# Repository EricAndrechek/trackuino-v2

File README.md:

The software and hardware for Trackuino, an open-source APRS tracker based on the Arduino platform. It was designed primarily to track high altitude balloons, so it has other handy features like reading temperature sensors and a buzzer for acoustic location.

Trackuino is intended for use by licensed radio amateurs.

# Features

-   Arduino form factor (support for Arduino Nano, Uno, and Mega)
-   Fully modular, choose the daughterboards you want to use and print/buy them and the motherboard that fits your Arduino
-   Onboard and external LED headers for module status indications
-   Internal/external temperature sensors to read temperature in and outside the payload
-   Active/passive buzzer support to ease acoustic payload location
-   Support for custom additional analog and digital sensors
-   Open source (GPLv2 license), both software and hardware. In other words, do whatever you want with it: modify it, add it to your project, etc. as long as you open-source your modifications as well.

## Modules

Choose whatever modules you want to use and add them onto your motherboard.

### GPS Module

-   Any GPS module that outputs NMEA strings (e.g. SiRF, UBLOX, etc.) is supported
-   GPS used needs 5V, GND, RX, and TX pins

### GSM Cellular Module

-   Allows sending data to a GSM network (e.g. AT&T, T-Mobile, etc.) via web requests or SMS messages
-   Configuration for message format and destination phone number or URL

### Radio Module

-   Radio: Radiometrix's HX1 (300 mW).
-   1200 bauds AFSK using 8-bit PWM
-   Sends out standard APRS position messages (latitude, longitude, altitude, course, speed and time).
-   SMA female plug for radio out

### SD Card Local Storage Module

-   OpenLog SD Card writing for an on-board copy of recorded data
-   Supports CSV format writing of data
-   Raw data dumping option
-   Custom pre-save formatting option (can convert raw analog input to temperature with given formula, etc.)

# Setup

Use the `Download ZIP` button or [click here](https://github.com/EricAndrechek/trackuino-v2/archive/refs/heads/main.zip) to get the source code and board schematics.

## Choosing Boards

Choose the motherboard you want to use based on what Arduino/MCU form factor you plan to use. The larger the Arduino/MCU and therefore motherboard, the more modules you will be able to add.

After selecting your motherboard, you can choose the modules you want to use. You can add as many modules as you want so long as they all fit on the motherboard. One of these modules needs to be the power daughterboard.

**Important**: Pay attention to the voltage your Arduino is using. If you are unsure, check [this page](https://learn.sparkfun.com/tutorials/arduino-comparison-guide/totally-tabular) to find out. If your MCU is 3.3V, you will need to print the 3.3V power daughterboard, if it is 5V, you will need to print the 5V power daughterboard.

Select all motherboards and module daughter boards you would like to use, and find somewhere online to get them printed.

## Soldering

Each module has a readme file that contains instructions for soldering. The boards also include labels on each component detailing what to solder where.

Each board's readme also includes a table of needed components to purchase to be used on your board.

## Software

If you are building for the Arduino platform you need the Arduino IDE. Get it from the [Arduino web site](https://arduino.cc/).

Unzip the software in your sketches directory and load it up by double-clicking on trackuino.ino.

The single most important configuration file is `config.h`. The file is self-documented. Here is where you set up your callsign, module settings, and more.

Some modules, like GSM, allow you to make additional configuration changes in their own custom, self-documented files so that you can do things like specify a JSON format for data to be sent through.

## Flashing

**Important**: When flashing the Arduino, remove the it from the motherboard. After flashing the firmware, you can plug it back in. The GPS, OpenLog, and the host computer share the same serial port on the AVR, so they will conflict when used together.

Within the Arduino IDE, be sure to select the correct board type for your Arduino.

While trackduino.ino is opened in the Arduino IDE, select the `Program` tab and click the `Upload` button.

## Debugging

In order to use serial debugging, you need to enable it in the `config.h` file, upload the code to the Arduino again, and then select the `Serial Monitor` tab.

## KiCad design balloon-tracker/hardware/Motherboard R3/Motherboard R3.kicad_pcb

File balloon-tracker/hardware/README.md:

# Hardware

To use the Trackuino-v2 code on your Arduino, you can either order a print of the PCB designed for your board type, and solder the necessary components onto the board, or you can use the schematics below to wire up your Arduino with a breadboard, protoboard, or something of that type.

## Components

<!-- TODO: update with current BOM -->

You will need the following components if you choose to solder it onto the PCB. Check the notes for each component to see if alternatives are recommended for breadboard wiring.

| Label | Qty | Component                            | Price                               | Provider                                                                                                                                                                                                                                                                                                          | Notes                                                                                                                                                                                                                                                                                                                |
| ----- | --- | ------------------------------------ | ----------------------------------- | ----------------------------------------------------------------------------------------------------------------------------------------------------------------------------------------------------------------------------------------------------------------------------------------------------------------- | -------------------------------------------------------------------------------------------------------------------------------------------------------------------------------------------------------------------------------------------------------------------------------------------------------------------- |
| A1    | 1   | Arduino                              | Depends on what Arduino you go with | [Arduino Store](https://store.arduino.cc/)                                                                                                                                                                                                                                                                        |                                                                                                                                                                                                                                                                                                                      |
| U1    | 1   | Radiometrix HX1                      | $50                                 | [Uptronics](https://store.uputronics.com/index.php?route=product/product&product_id=63), [Radiometrix](https://radiometrix.mybigcommerce.com/hx1-vhf-narrow-band-fm-300mw-transmitter-standard-frequencies-144-390-144-800-and-169-4125mhz/)                                                                      |                                                                                                                                                                                                                                                                                                                      |
| J1    | 1   | SMA Female Connector                 | $1.40                               | [Mouser](https://www.mouser.com/ProductDetail/LPRS/SMA-CONNECTOR?qs=j%252B1pi9TdxUYkOiITvzJM8A%3D%3D), [Uptronics](https://store.uputronics.com/index.php?route=product/product&path=63&product_id=79)                                                                                                            |                                                                                                                                                                                                                                                                                                                      |
|       | 1   | SMA Flexible Extender                | $10                                 | [Uptronics](https://store.uputronics.com/index.php?route=product/product&path=63&product_id=58), [Mouser](https://www.mouser.com/ProductDetail/Amphenol-RF/135109-02-06.00?qs=3WadRV20yGyRMmeZhUPdRQ%3D%3D), [B&H](https://www.bhphotovideo.com/c/product/961489-REG/startech_rpsma10mf_10_rp_sma_to_rp_sma.html) | If antenna is attached straight to board, no flexible extender is needed.                                                                                                                                                                                                                                            |
|       | 1   | Antenna                              | $40                                 | [MFJ](https://mfjenterprises.com/products/mfj-1717s)                                                                                                                                                                                                                                                              |                                                                                                                                                                                                                                                                                                                      |
| U2    | 1   | GPS                                  | $12                                 | [Amazon](https://www.amazon.com/Microcontroller-Compatible-Sensitivity-Navigation-Positioning/dp/B07P8YMVNT)                                                                                                                                                                                                      | Any GPS module will work, so long as it is 5V, and outputs NMEA strings. If you are using the PCB design, having one with TX RX GND and VIN all in a row will allow it to be plug-and-play without any wire re-routing. When purchasing a GPS module, please make note of the GPS limitations on speed and altitude. |
| U3    | 1   | Bi-Directional Logic Level Converter | $3.50                               | [SparkFun](https://www.sparkfun.com/products/12009)                                                                                                                                                                                                                                                               | On a breadboard, you could skip this step and instead build voltage dividers for the RX and TX lines to step them down from 5V to 3.3V.                                                                                                                                                                              |
| U4    | 1   | OpenLog                              | $16.95                              | [SparkFun](https://www.sparkfun.com/products/13712)                                                                                                                                                                                                                                                               |                                                                                                                                                                                                                                                                                                                      |
| U5    | 1   | 3.3V LDO                             | $0.67                               | [Mouser](https://www.mouser.com/ProductDetail/STMicroelectronics/LD1117S33TR?qs=edoyzKMbmhntQZx4BFmoqw%3D%3D)                                                                                                                                                                                                     | Any 3.3V through-hole LDO *should* work for a breadboard, just make note of pin orientations. A LD1117V33 with a footprint of SOT223 is what you are looking for. Here is an example on [Mouser](https://www.mouser.com/ProductDetail/STMicroelectronics/LD1117V50?qs=arR7071Fstdq5MS%2FejBvyQ%3D%3D)                |
| U6    | 1   | 5V LDO                               | $0.67                               | [Mouser](https://www.mouser.com/ProductDetail/STMicroelectronics/LD1117S50TR?qs=eQN2Ig5lfEwsh0kTXN%2FkTg%3D%3D)                                                                                                                                                                                                   | Any 5V through-hole LDO *should* work for a breadboard, just make note of pin orientations. A LD1117V50 with a footprint of SOT223 is what you are looking for.                                                                                                                                                      |
| C1-C3 | 3   | 0.1uF                                | $0.14                               | [Mouser](https://www.mouser.com/ProductDetail/KEMET/C0603C104K3RAC7013?qs=nAEW9fCjKd89XJLxiep6YQ%3D%3D)                                                                                                                                                                                                           | Any 0.1uF Capacitor should work.                                                                                                                                                                                                                                                                                     |
| SW1   | 1   | Push Button                          | $2.50 for 20                        | [Adafruit](https://www.adafruit.com/product/367)                                                                                                                                                                                                                                                                  | You can pretty safely avoid installing this at all and just use the reset button on your Arduino.                                                                                                                                                                                                                    |
| BZ1   | 1   | Buzzer (active or passive)           | $0.30                               | [Active Buzzer - Addicore](https://www.addicore.com/Active-Buzzer-5V-p/ad146.htm), [Passive Busser - Addicore](https://www.addicore.com/Passive-Buzzer-p/ad319.htm)                                                                                                                                               | Active buzzer is more versatile and therefore recommended.                                                                                                                                                                                                                                                           |
| U7    | 2   | TMP36 Temperature Sensor             | $1.60                               | [SparkFun](https://www.sparkfun.com/products/10988)                                                                                                                                                                                                                                                               | One is to be hooked up to terminal blocks to be wired outside of your Trackuino-v2's enclosure, the other is for inside said enclosure.                                                                                                                                                                              |
| P1    | 1   | 2-Wide Terminal Blocks               | $0.65                               | [Mouser](https://www.mouser.com/ProductDetail/CUI-Devices/TB002-500-02BE?qs=vLWxofP3U2x9716kcgva%2Fw%3D%3D)                                                                                                                                                                                                       | Any terminal blocks will work, screwed or not, as long as they fit the same pin dimensions. Alternatively you can skip terminal blocks entirely and solder to the holes they leave on the board. Terminal blocks shouldn't be purchased for a breadboard.                                                            |
| U8    | 1   | 3-Wide Terminal Blocks               | $0.66                               | [Mouser](https://www.mouser.com/ProductDetail/CUI-Devices/TBL004V-508-02BE-2GY?qs=UXgszm6BlbFJXFFgC%2FsssQ%3D%3D)                                                                                                                                                                                                 | Same as previous terminal block note.                                                                                                                                                                                                                                                                                |
| D1-D3 | 3   | LEDs                                 | $4                                  | [Amazon](https://www.amazon.com/JABINCO-Circuit-Assorted-Science-Experiment/dp/B0827KYRFH/ref=sr_1_8?crid=QILAHDHBQAH3&keywords=through-hole+leds&qid=1660157838&sprefix=through-ho%2Caps%2C866&sr=8-8)                                                                                                           | Just any 3 LEDs. Different colors for each makes it easier to differentiate which status LED is which.                                                                                                                                                                                                               |
| R1-R3 | 3   | 330 Ohm Resistors                    | $1.05                               | [SparkFun](https://www.sparkfun.com/products/14490)                                                                                                                                                                                                                                                               | Other resistances would work too, 330 is not an exact requirement.                                                                                                                                                                                                                                                   |

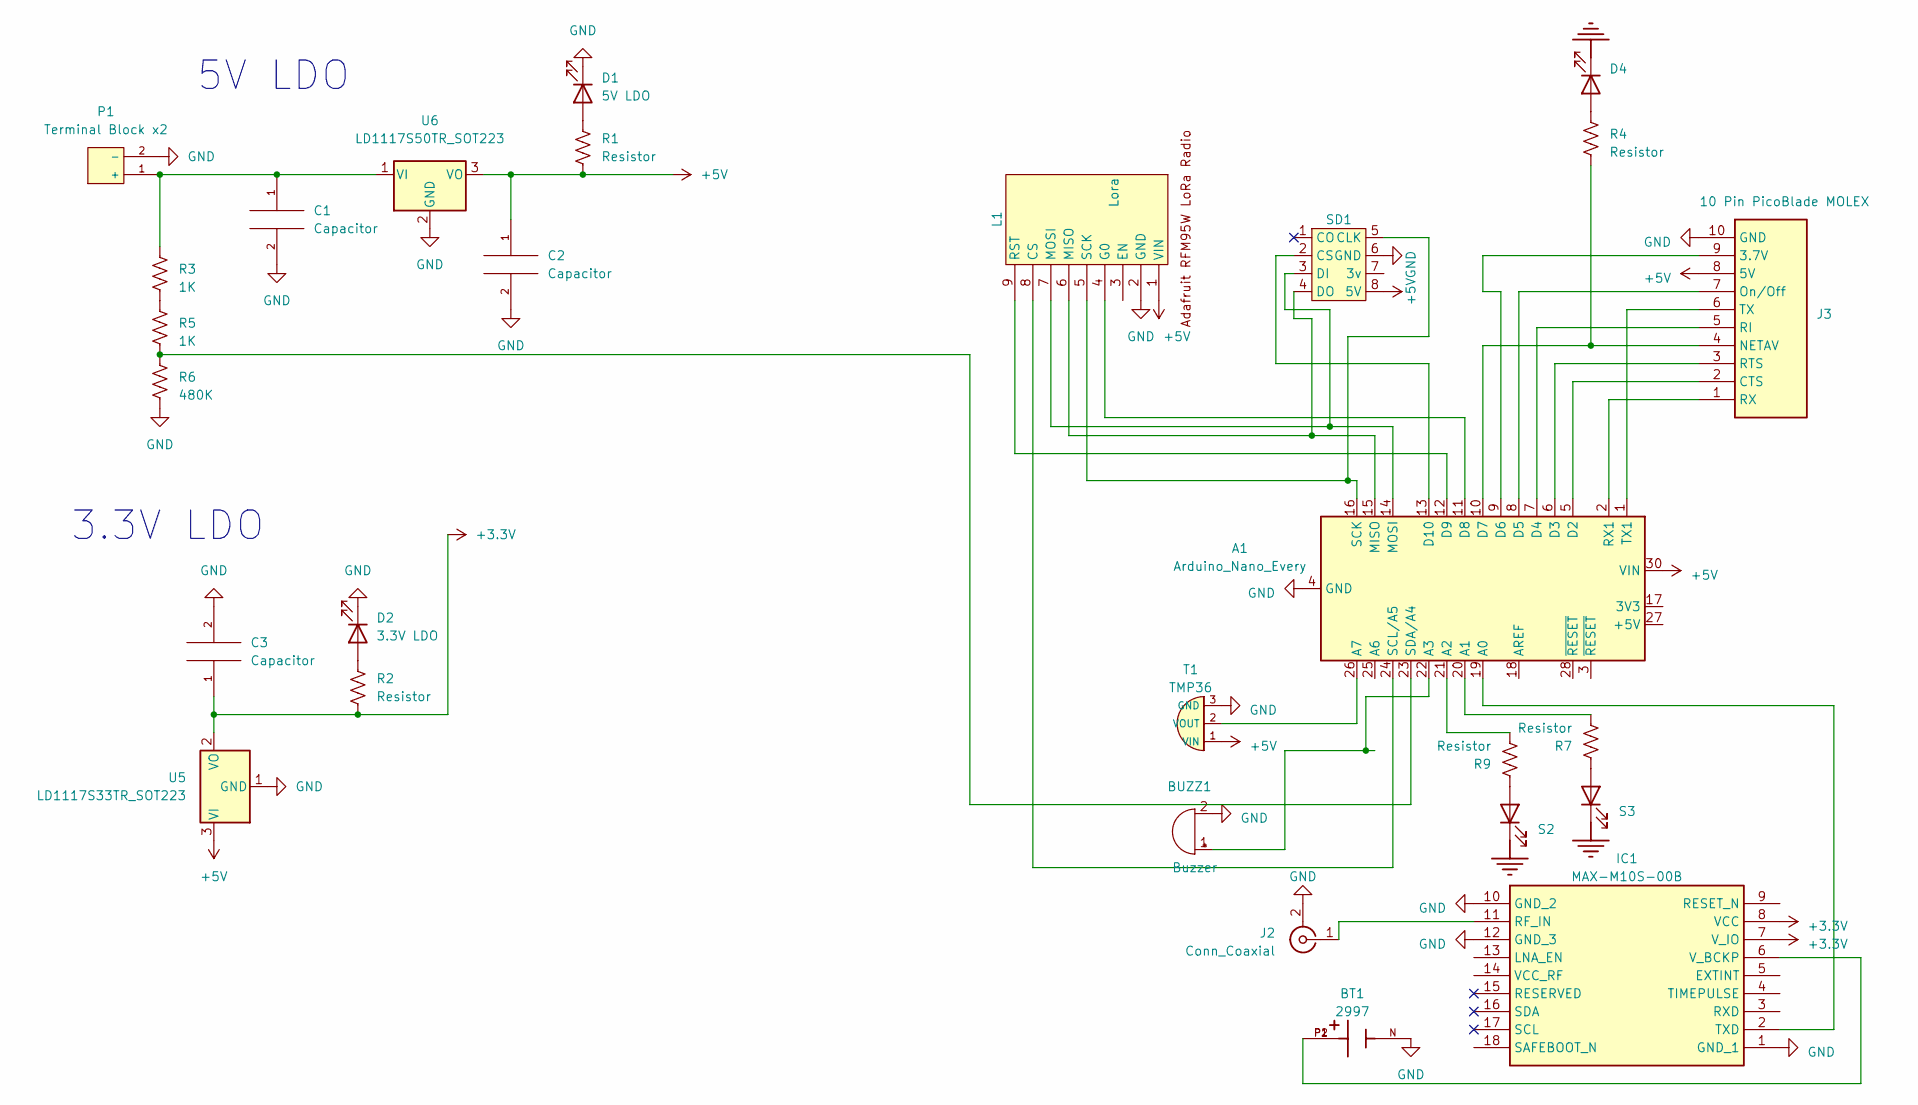
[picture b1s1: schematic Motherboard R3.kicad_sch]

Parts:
A1: Arduino_Nano_Every; Arduino_Nano
BT1: 2997; BAT_2997; PARTREV D
BUZZ1: Buzzer; XDCR_AI-1224-TWT-5V-R
C1, C2, C3: Capacitor; C_1206_3216Metric
D1: 5V LDO; LED_1206_3216Metric
D2: 3.3V LDO; LED_1206_3216Metric
D4: NETAV; LED_1206_3216Metric
IC1: MAX-M10S-00B; MAXM10S00B; Mouser Part Number 377-MAX-M10S-00B
J2: Conn_Coaxial; Molex SMA Edge Mount
J3: 10 Pin PicoBlade MOLEX; Molex_PicoBlade_53048-1010_1x10_P1.25mm_Horizontal; Mouser Part Number 538-53048-1010
L1: Lora; Adafruit LoRa Breakout
P1: Terminal Block x2
R1, R2, R4, R7, R9: Resistor; R_1206_3216Metric
R3, R5: 1K; R_1206_3216Metric
R6: 480K; R_1206_3216Metric
S2, S3: NETAV; LED_1206_3216Metric
SD1: Adafruit 5V SD Breakout Brd+
T1: TMP36
U5: LD1117S33TR_SOT223; SOT-223-3_TabPin2
U6: LD1117S50TR_SOT223; SOT-223-3_TabPin2

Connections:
+3.3V: C3.1, IC1.7 (V_IO), IC1.8 (VCC), R2.2, U5.2 (VO)
+5V: A1.30 (VIN), C2.1, J3.8 (5V), L1.1 (VIN), R1.2, SD1.8 (5V), T1.1 (VIN), U5.3 (VI), U6.3 (VO)
GND: A1.4 (GND), A1.29 (GND), BT1.N, BUZZ1.2 (+), C1.2, C2.2, C3.2, D1.1 (K), D2.1 (K), D4.1 (K), IC1.1 (GND_1), IC1.10 (GND_2), IC1.12 (GND_3), J2.2 (Ext), J3.10 (GND), L1.2 (GND), P1.2 (-), R6.2, S2.1 (K), S3.1 (K), SD1.6 (GND), T1.3 (GND), U5.1 (GND), U6.2 (GND)
unnamed: A1.19 (A0), IC1.2 (TXD)
unnamed: A1.20 (A1), R7.2
unnamed: A1.21 (A2), R9.2
unnamed: A1.22 (A3), BUZZ1.1 (-)
unnamed: A1.26 (A7), T1.2 (VOUT)
unnamed: A1.5 (D2), J3.2 (CTS)
unnamed: A1.6 (D3), J3.3 (RTS)
unnamed: A1.7 (D4), J3.5 (RI)
unnamed: A1.8 (D5), J3.7 (On/Off)
unnamed: A1.9 (D6), J3.9 (3.7V)
unnamed: A1.10 (D7), J3.4 (NETAV), R4.2
unnamed: A1.11 (D8), L1.4 (G0)
unnamed: A1.12 (D9), L1.9 (RST)
unnamed: A1.13 (D10), SD1.2 (CS)
unnamed: A1.15 (MISO), L1.6 (MISO), SD1.4 (DO)
unnamed: A1.14 (MOSI), L1.7 (MOSI), SD1.3 (DI)
unnamed: A1.2 (RX1), J3.1 (RX)
unnamed: A1.16 (SCK), L1.5 (SCK), SD1.5 (CLK)
unnamed: A1.24 (SCL/A5), L1.8 (CS)
unnamed: A1.23 (SDA/A4), R5.2, R6.1
unnamed: A1.1 (TX1), J3.6 (TX)
unnamed: D1.2 (A), R1.1
unnamed: D2.2 (A), R2.1
unnamed: D4.2 (A), R4.1
unnamed: IC1.11 (RF_IN), J2.1 (In)
unnamed: BT1.P1, BT1.P2, IC1.6 (V_BCKP)
unnamed: C1.1, P1.1 (+), R3.1, U6.1 (VI)
unnamed: R3.2, R5.1
unnamed: R9.1, S2.2 (A)
unnamed: R7.1, S3.2 (A)

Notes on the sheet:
3.3V LDO
5V LDO

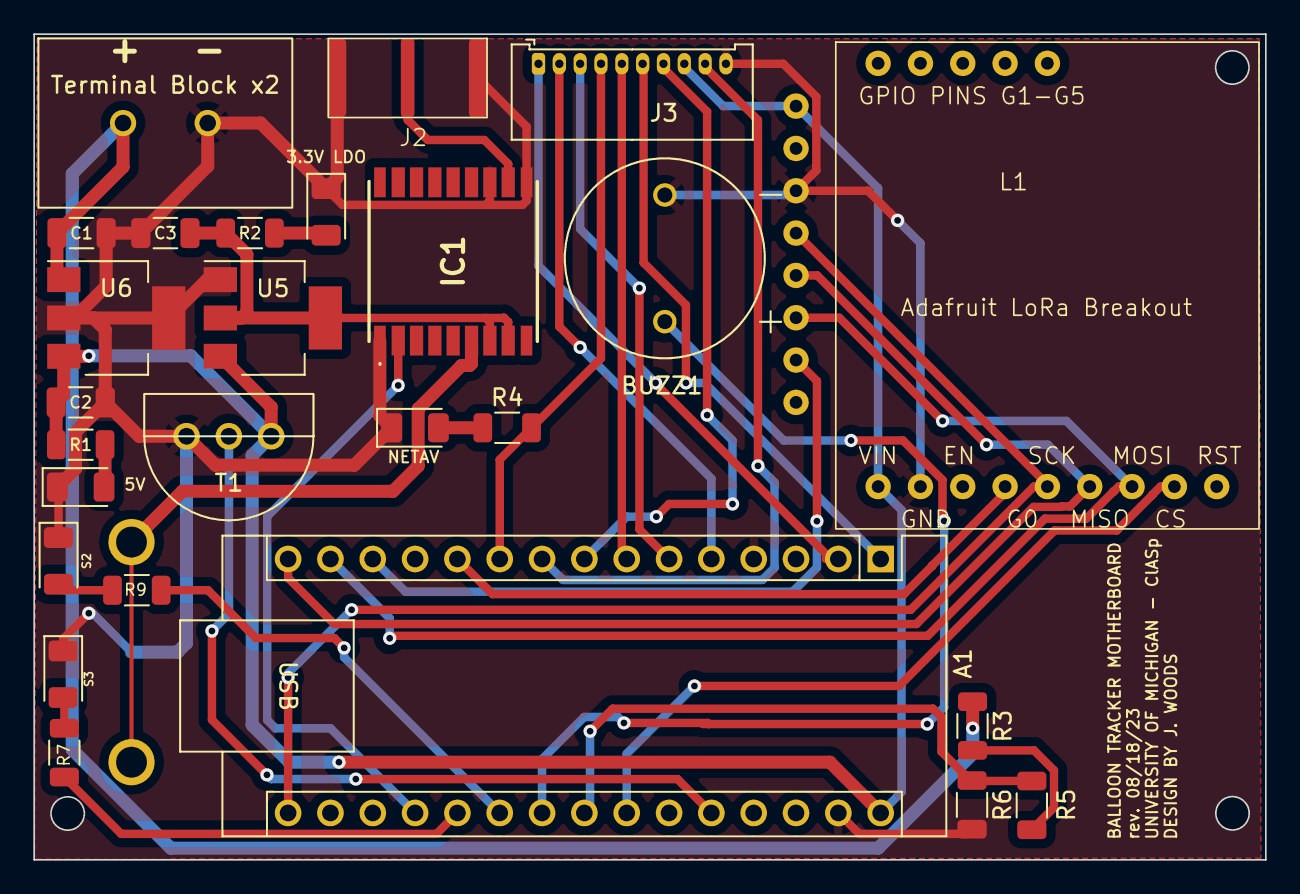
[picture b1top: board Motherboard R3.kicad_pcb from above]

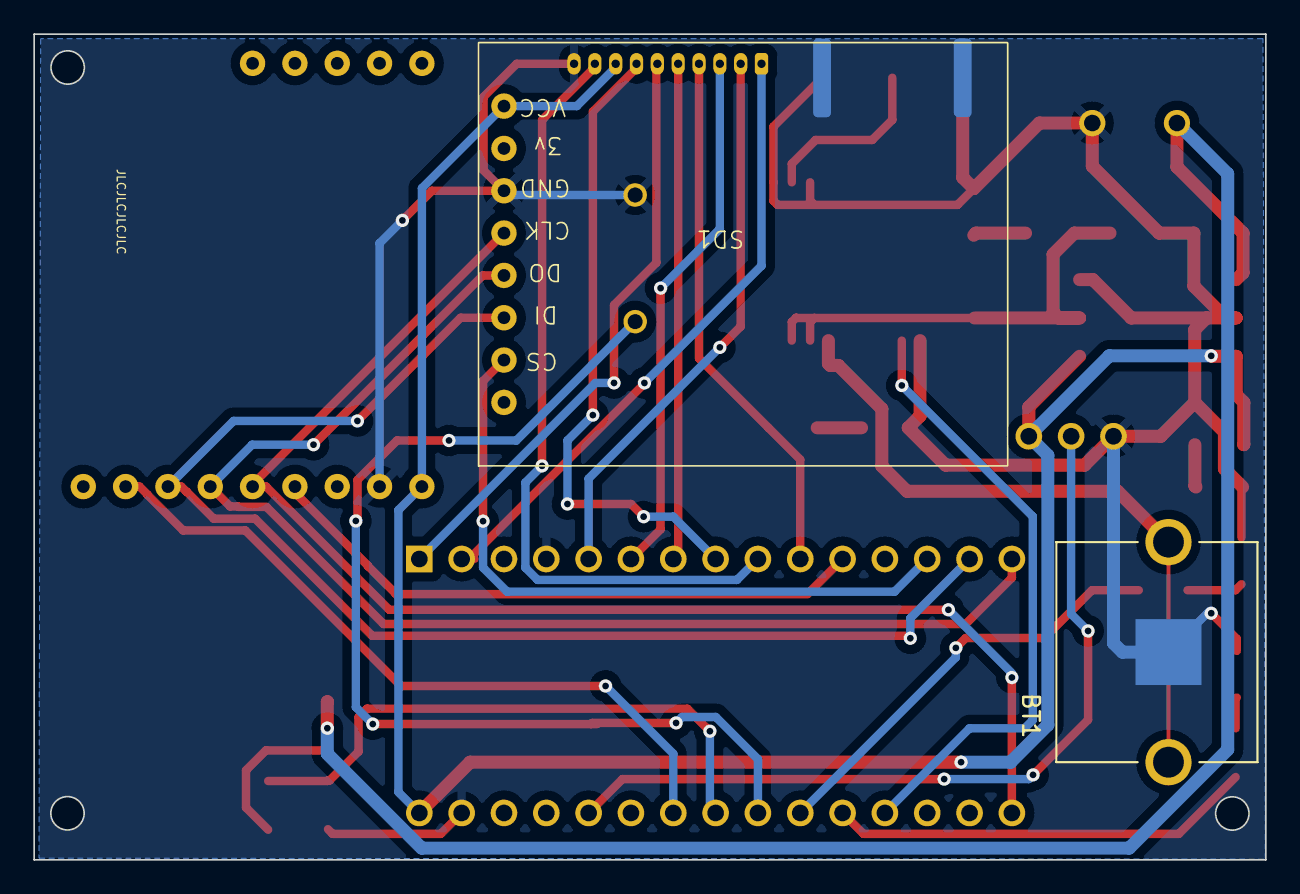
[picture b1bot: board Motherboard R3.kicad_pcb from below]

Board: 2 copper layers, 73.9 x 49.5 mm, 28 parts (2 on the bottom side), 32 nets.

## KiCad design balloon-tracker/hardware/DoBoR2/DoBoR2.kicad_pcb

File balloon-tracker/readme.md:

The software and hardware for Trackuino-v2, an open-source APRS tracker based on the Arduino platform. It was designed primarily to track high altitude balloons, so it has other handy features like reading temperature sensors and a buzzer for acoustic location.

Trackuino is intended for use by licensed radio amateurs.

# Features

- Arduino form factor (support for Arduino Nano, others coming soon:tm:)
- Fully modular, choose the daughterboard you want to use and print/buy them and the motherboard that fits your Arduino
- Onboard and external LED headers for module status indications
- Internal/external temperature sensors to read temperature in and outside the payload
- Active/passive buzzer support to ease acoustic payload location
- Support for custom additional analog and digital sensors
- Open source (GPLv2 license), both software and hardware. In other words, do whatever you want with it: modify it, add it to your project, etc. as long as you open-source your modifications as well.

## Built-In Modules

The following modules are included on the motherboard:

### GPS Module

- UBLOX MAX-M10S GPS chip

### MicroSD Card Local Storage

- MicroSD card writing for an on-board copy of recorded data
- Supports CSV format writing of data
- Raw data dumping option
- Custom pre-save formatting option (can convert raw analog input to temperature with given formula, etc.)

### LoRa Radio Module

- Radio: RFM95W
- 915MHz frequency (tuneable to others for different regions)
- 20dBm output power
- Used to send data in addition to daughterboard modules, allows 2-way communication

### Flight Termination Unit (FTU) Transmitter Module

- Modified [315MHz transmitter](https://www.adafruit.com/product/1095) for sending digital FTU signals

### Buzzer

- Active buzzer for acoustic payload location
- Supports GPS readings for variable buzzing based on altitude or satellite lock

### Temperature Sensors

- Internal and external temperature sensors
- TMP36 analog temperature sensor

### LED Indicators

- Onboard and external LED headers for module status indications
- Customizable LED blinking patterns for different module statuses

## Daughterboard Modules

In addition to the main motherboard, you can attach any one of the following daughterboards to the motherboard via the molex connector for additional functionality.

### GSM Cellular Module

**Note**: Work in progress

- Allows sending data to a GSM network (e.g. AT&T, T-Mobile, etc.) via web requests or SMS messages
- Configuration for message format and destination phone number or URL

### HAM Radio APRS Module

- Radio: DORJI DRA818V
- 1200 baud AFSK using 8-bit PWM
- Sends out standard APRS position messages (latitude, longitude, altitude, course, speed and time), and telemetry data
- SMA plug for radio out

### Iridium Satellite Module

- RockBLOCK 9603 Iridium satellite modem

# Setup

Use the `Download ZIP` button or [click here](https://github.com/EricAndrechek/trackuino-v2/archive/refs/heads/main.zip) to get the source code and board schematics. The hardware is designed in KiCad and the software is written in C++ for the Arduino platform.

Navigate to the `balloon-tracker/hardware` directory to find the KiCad files for the motherboard and daughterboard modules. Navigate to the `balloon-tracker/software` directory to find the Arduino sketch for the firmware.

## Choosing Boards

Choose the motherboard you want to use based on what Arduino/MCU form factor you plan to use.

After selecting your motherboard, you can choose the daughterboard you want to use.

Select all motherboards and daughterboards you would like to use, and find somewhere online to get them printed. You will need to open the KiCad files in KiCad and export the gerber files (and drill files) to send to a PCB printing service.

## Soldering

Each module has a readme file that contains instructions for soldering. The boards also include labels on each component detailing what to solder where.

Each board's readme also includes a table of needed components to purchase to be used on your board.

## Software

If you are building for the Arduino platform you need the Arduino IDE. Get it from the [Arduino web site](https://arduino.cc/).

Unzip the software in your sketches directory and load it up by double-clicking on trackuino.ino.

The single most important configuration file is `config.h`. The file is self-documented. Here is where you set up your callsign, module settings, and more.

Some daughterboards, like GSM, allow you to make additional configuration changes in their own custom, self-documented files so that you can do things like specify a JSON format for data to be sent through.

## Flashing

**Important**: When flashing the Arduino, remove the it from the motherboard. After flashing the firmware, you can plug it back in. The GPS, microSD card module, and the host computer share the same serial port on the AVR, so they will conflict when used together.

Within the Arduino IDE, be sure to select the correct board type for your Arduino.

While `software.ino` is opened in the Arduino IDE, select the `Program` tab and click the `Upload` button.

## Debugging

In order to use serial debugging, you need to enable it in the `config.h` file, upload the code to the Arduino again, and then select the `Serial Monitor` tab.

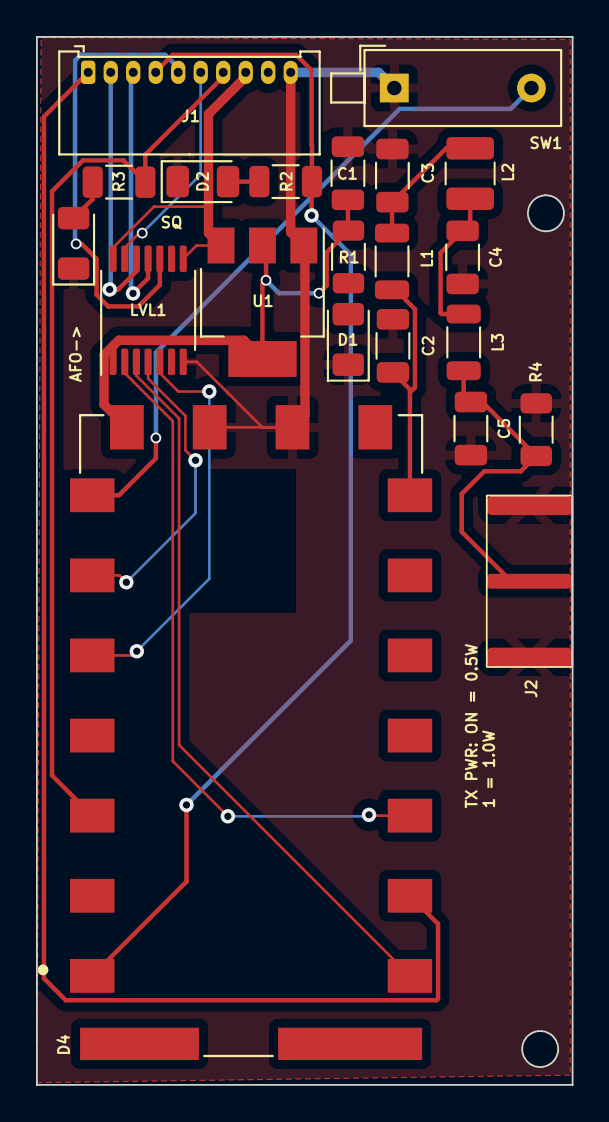
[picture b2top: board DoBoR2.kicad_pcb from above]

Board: 2 copper layers, 29.8 x 58.2 mm, 21 parts (0 on the bottom side), 22 nets.

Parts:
C1: Capacitor; C_1206_3216Metric
C2, C5: 20 pF; C_1206_3216Metric
C3, C4: 36 pF; C_1206_3216Metric
D1: 3.3V LDO; LED_1206_3216Metric
D2: SQUELCH; LED_1206_3216Metric
D3: AF_OUT; LED_1206_3216Metric
D4: DORJI_DRA818V
J1: 10 Pin PicoBlade MOLEX; Molex_PicoBlade_53048-1010_1x10_P1.25mm_Horizontal
J2: Conn_Coaxial; Molex SMA Edge Mount
L1, L3: 56 nH; L_1206_3216Metric
L2: 68 nH; L_1210_3225Metric
LVL1: TXU0104BQAR; TSSOP-14_4.4x5mm_P0.65mm
R1, R2, R3: Resistor; R_1206_3216Metric
R4: 50 ohm; R_1206_3216Metric
SW1: SW_DIP_x01; SW_DIP_SPSTx01_Piano_10.8x4.1mm_W7.62mm_P2.54mm
U1: LD1117S33TR_SOT223; SOT-223-3_TabPin2

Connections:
+3.3V: C1.1, D4.8 (VIN), LVL1.1 (VCC_A), R1.2, U1.2 (VO)
+5V: J1.8 (5V), LVL1.8 (OE), LVL1.14 (VCC_B), U1.3 (VI)
GND: C1.2, C2.2, C3.2, C4.2, C5.2, D1.1 (K), D2.1 (K), D3.1 (K), D4.9 (GND), D4.10 (GND), J1.10 (GND), J2.2 (Ext), LVL1.7 (GND), R4.2, SW1.1, U1.1 (GND)
unnamed: C3.1, L1.2, L2.1
unnamed: C4.1, L2.2, L3.1
unnamed: D1.2 (A), R1.1
unnamed: D2.2 (A), R2.1
unnamed: D3.2 (A), R3.1
unnamed: D4.3 (AF_OUT), J1.7 (On/Off), R3.2
unnamed: C2.1, D4.12 (ANT), L1.1
unnamed: D4.7 (H/L), SW1.2
unnamed: D4.18 (MIC_IN), LVL1.3 (A2)
unnamed: D4.6 (PD), LVL1.4 (A3)
unnamed: D4.5 (PTT), LVL1.5 (A4)
unnamed: D4.16 (RXD), LVL1.2 (A1)
unnamed: D4.1 (SQ), J1.4 (NETAV), R2.2
unnamed: D4.17 (TXD), J1.1 (RX)
unnamed: J1.2 (CTS), LVL1.12 (B2Y)
unnamed: J1.5 (RI), LVL1.10 (B4Y)
unnamed: J1.3 (RTS), LVL1.11 (B3Y)
unnamed: J1.6 (TX), LVL1.13 (B1Y)
unnamed: C5.1, J2.1 (In), L3.2, R4.1

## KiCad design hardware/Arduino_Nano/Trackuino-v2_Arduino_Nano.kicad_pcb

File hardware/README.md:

# Hardware

To use the Trackuino-v2 code on your Arduino, you can either order a print of the PCB designed for your board type, and solder the necessary components onto the board, or you can use the schematics below to wire up your Arduino with a breadboard, protoboard, or something of that type.

## Components

You will need the following components if you choose to solder it onto the PCB. Check the notes for each component to see if alternatives are recommended for breadboard wiring.

| Label | Qty | Component | Price | Provider | Notes |
|---|---|---|---|---|---|
| A1 | 1 | Arduino | Depends on what Arduino you go with | [Arduino Store](https://store.arduino.cc/) |  |
| U1 | 1 | Radiometrix HX1 | $50 | [Uptronics](https://store.uputronics.com/index.php?route=product/product&product_id=63), [Radiometrix](https://radiometrix.mybigcommerce.com/hx1-vhf-narrow-band-fm-300mw-transmitter-standard-frequencies-144-390-144-800-and-169-4125mhz/) |  |
| J1 | 1 | SMA Female Connector | $1.40 | [Mouser](https://www.mouser.com/ProductDetail/LPRS/SMA-CONNECTOR?qs=j%252B1pi9TdxUYkOiITvzJM8A%3D%3D), [Uptronics](https://store.uputronics.com/index.php?route=product/product&path=63&product_id=79) |  |
|  | 1 | SMA Flexible Extender | $10 | [Uptronics](https://store.uputronics.com/index.php?route=product/product&path=63&product_id=58), [Mouser](https://www.mouser.com/ProductDetail/Amphenol-RF/135109-02-06.00?qs=3WadRV20yGyRMmeZhUPdRQ%3D%3D), [B&H](https://www.bhphotovideo.com/c/product/961489-REG/startech_rpsma10mf_10_rp_sma_to_rp_sma.html) | If antenna is attached straight to board, no flexible extender is needed. |
|  | 1 | Antenna | $40 | [MFJ](https://mfjenterprises.com/products/mfj-1717s) |  |
| U2 | 1 | GPS | $12 | [Amazon](https://www.amazon.com/Microcontroller-Compatible-Sensitivity-Navigation-Positioning/dp/B07P8YMVNT) | Any GPS module will work, so long as it is 5V, and outputs NMEA strings. If you are using the PCB design, having one with TX RX GND and VIN all in a row will allow it to be plug-and-play without any wire re-routing. When purchasing a GPS module, please make note of the GPS limitations on speed and altitude. |
| U3 | 1 | Bi-Directional Logic Level Converter | $3.50 | [SparkFun](https://www.sparkfun.com/products/12009) | On a breadboard, you could skip this step and instead build voltage dividers for the RX and TX lines to step them down from 5V to 3.3V. |
| U4 | 1 | OpenLog | $16.95 | [SparkFun](https://www.sparkfun.com/products/13712) |  |
| U5 | 1 | 3.3V LDO | $0.67 | [Mouser](https://www.mouser.com/ProductDetail/STMicroelectronics/LD1117S33TR?qs=edoyzKMbmhntQZx4BFmoqw%3D%3D) | Any 3.3V through-hole LDO *should* work for a breadboard, just make note of pin orientations. A LD1117V33 with a footprint of SOT223 is what you are looking for. Here is an example on [Mouser](https://www.mouser.com/ProductDetail/STMicroelectronics/LD1117V50?qs=arR7071Fstdq5MS%2FejBvyQ%3D%3D) |
| U6 | 1 | 5V LDO | $0.67 | [Mouser](https://www.mouser.com/ProductDetail/STMicroelectronics/LD1117S50TR?qs=eQN2Ig5lfEwsh0kTXN%2FkTg%3D%3D) | Any 5V through-hole LDO *should* work for a breadboard, just make note of pin orientations. A LD1117V50 with a footprint of SOT223 is what you are looking for. |
| C1-C3 | 3 | 0.1uF | $0.14 | [Mouser](https://www.mouser.com/ProductDetail/KEMET/C0603C104K3RAC7013?qs=nAEW9fCjKd89XJLxiep6YQ%3D%3D) | Any 0.1uF Capacitor should work.  |
| SW1 | 1 | Push Button | $2.50 for 20 | [Adafruit](https://www.adafruit.com/product/367) | You can pretty safely avoid installing this at all and just use the reset button on your Arduino. |
| BZ1 | 1 | Buzzer (active or passive) | $0.30 | [Active Buzzer - Addicore](https://www.addicore.com/Active-Buzzer-5V-p/ad146.htm), [Passive Busser - Addicore](https://www.addicore.com/Passive-Buzzer-p/ad319.htm) | Active buzzer is more versatile and therefore recommended.  |
| U7 | 2 | TMP36 Temperature Sensor | $1.60 | [SparkFun](https://www.sparkfun.com/products/10988) | One is to be hooked up to terminal blocks to be wired outside of your Trackuino-v2's enclosure, the other is for inside said enclosure. |
| P1 | 1 | 2-Wide Terminal Blocks | $0.65 | [Mouser](https://www.mouser.com/ProductDetail/CUI-Devices/TB002-500-02BE?qs=vLWxofP3U2x9716kcgva%2Fw%3D%3D) | Any terminal blocks will work, screwed or not, as long as they fit the same pin dimensions. Alternatively you can skip terminal blocks entirely and solder to the holes they leave on the board. Terminal blocks shouldn't be purchased for a breadboard. |
| U8 | 1 | 3-Wide Terminal Blocks | $0.66 | [Mouser](https://www.mouser.com/ProductDetail/CUI-Devices/TBL004V-508-02BE-2GY?qs=UXgszm6BlbFJXFFgC%2FsssQ%3D%3D) | Same as previous terminal block note. |
| D1-D3 | 3 | LEDs | $4 | [Amazon](https://www.amazon.com/JABINCO-Circuit-Assorted-Science-Experiment/dp/B0827KYRFH/ref=sr_1_8?crid=QILAHDHBQAH3&keywords=through-hole+leds&qid=1660157838&sprefix=through-ho%2Caps%2C866&sr=8-8) | Just any 3 LEDs. Different colors for each makes it easier to differentiate which status LED is which. |
| R1-R3 | 3 | 330 Ohm Resistors | $1.05 | [SparkFun](https://www.sparkfun.com/products/14490) | Other resistances would work too, 330 is not an exact requirement. |

## Wiring

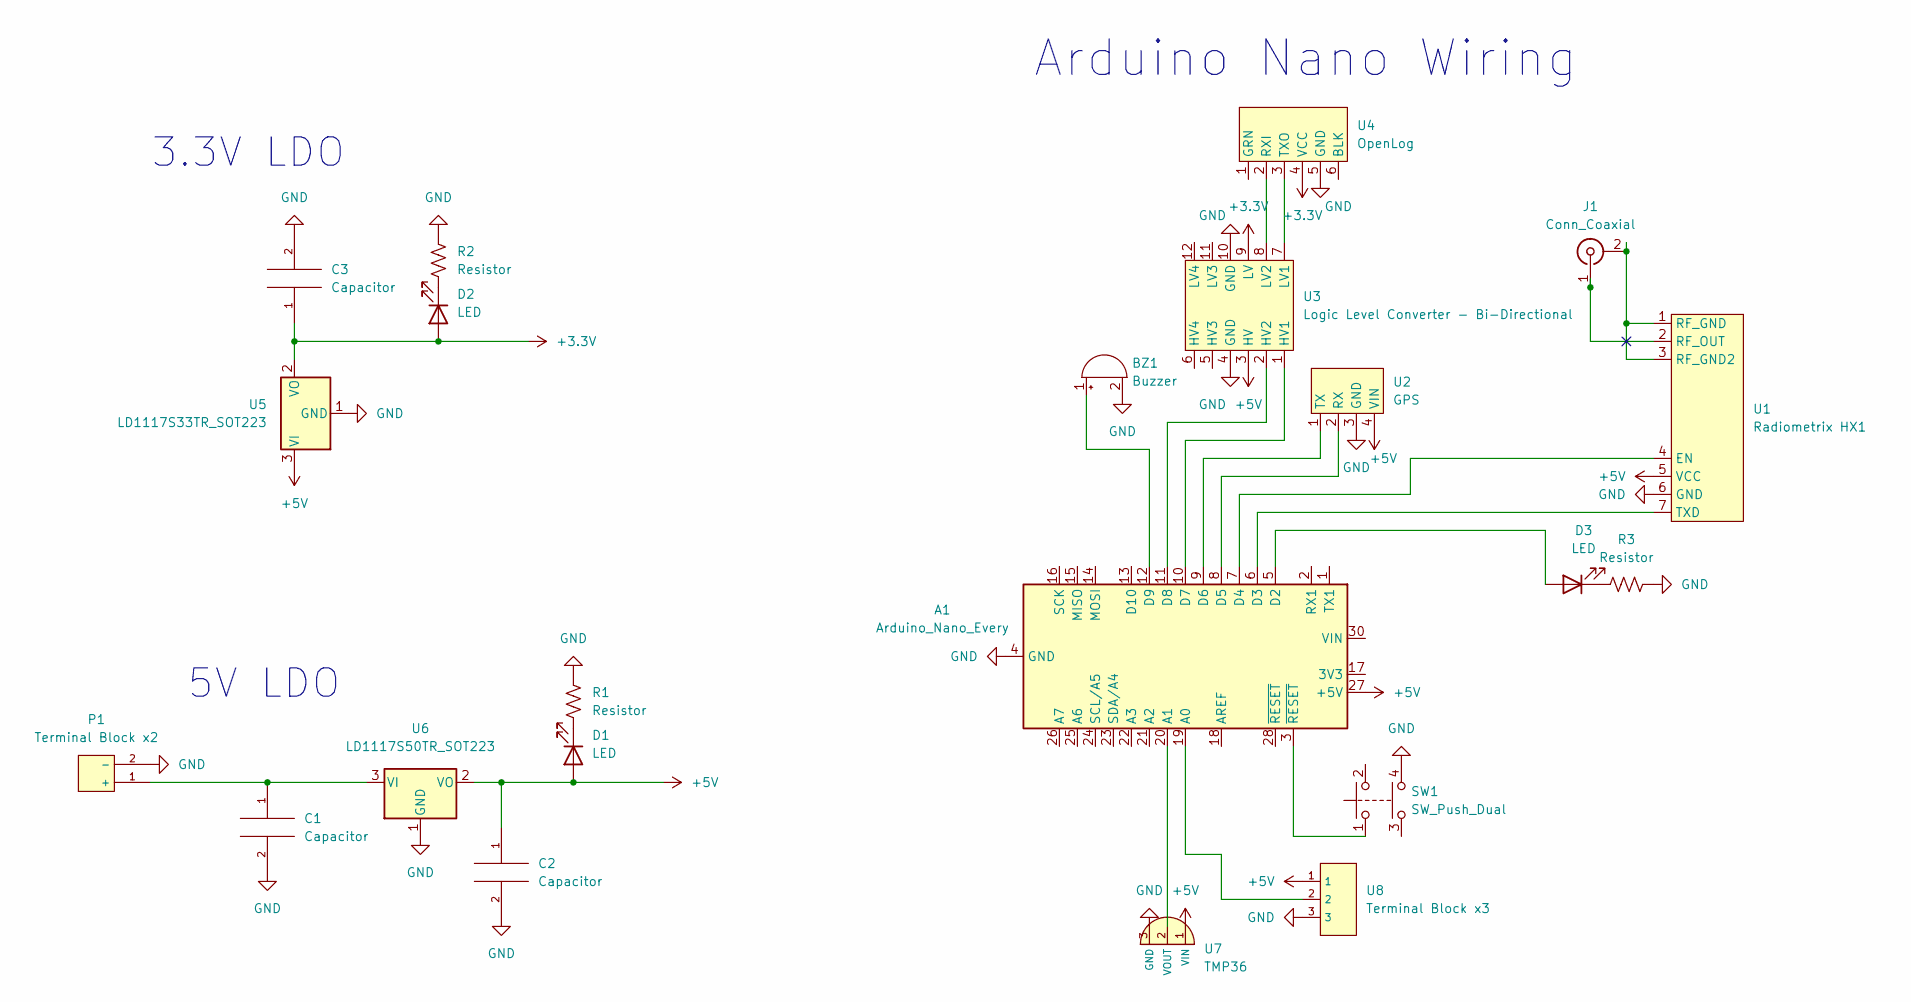
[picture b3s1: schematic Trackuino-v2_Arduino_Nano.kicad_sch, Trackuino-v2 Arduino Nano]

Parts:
A1: Arduino_Nano_Every; Arduino_Nano
BZ1: Buzzer
C1, C2, C3: Capacitor
D1, D2, D3: LED
J1: Conn_Coaxial; SMA Jack
P1: Terminal Block x2
R1, R2, R3: Resistor
SW1: SW_Push_Dual; Button
U1: Radiometrix HX1
U2: GPS
U3: Logic Level Converter - Bi-Directional
U4: OpenLog
U5: LD1117S33TR_SOT223; SOT-223-3_TabPin2
U6: LD1117S50TR_SOT223; SOT-223-3_TabPin2
U7: TMP36
U8: Terminal Block x3

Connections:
+3.3V: C3.1, D2.2 (A), U3.9 (LV), U4.4 (VCC), U5.2 (VO)
+5V: A1.27 (+5V), C2.1, D1.2 (A), U1.5 (VCC), U2.4 (VIN), U3.3 (HV), U5.3 (VI), U6.2 (VO), U7.1 (VIN), U8.1
GND: A1.4 (GND), A1.29 (GND), BZ1.2 (+), C1.2, C2.2, C3.2, P1.2 (-), R1.1, R2.1, R3.1, SW1.4, U1.6 (GND), U2.3 (GND), U3.4 (GND), U3.10 (GND), U4.5 (GND), U5.1 (GND), U6.1 (GND), U7.3 (GND), U8.3
unnamed: A1.3 (~RESET), SW1.1
unnamed: A1.5 (D2), D3.2 (A)
unnamed: A1.6 (D3), U1.7 (TXD)
unnamed: A1.7 (D4), U1.4 (EN)
unnamed: A1.8 (D5), U2.2 (RX)
unnamed: A1.9 (D6), U2.1 (TX)
unnamed: A1.10 (D7), U3.1 (HV1)
unnamed: A1.11 (D8), U3.2 (HV2)
unnamed: A1.12 (D9), BZ1.1 (-)
unnamed: A1.19 (A0), U8.2
unnamed: A1.20 (A1), U7.2 (VOUT)
unnamed: C1.1, P1.1 (+), U6.3 (VI)
unnamed: D1.1 (K), R1.2
unnamed: D2.1 (K), R2.2
unnamed: D3.1 (K), R3.2
unnamed: J1.1 (In), U1.2 (RF_OUT)
unnamed: J1.2 (Ext), U1.1 (RF_GND), U1.3 (RF_GND2)
unnamed: U3.7 (LV1), U4.3 (TXO)
unnamed: U3.8 (LV2), U4.2 (RXI)

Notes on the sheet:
5V LDO
3.3V LDO
Arduino Nano Wiring

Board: 2 copper layers, 22 parts (0 on the bottom side), 22 nets, no tracks yet.

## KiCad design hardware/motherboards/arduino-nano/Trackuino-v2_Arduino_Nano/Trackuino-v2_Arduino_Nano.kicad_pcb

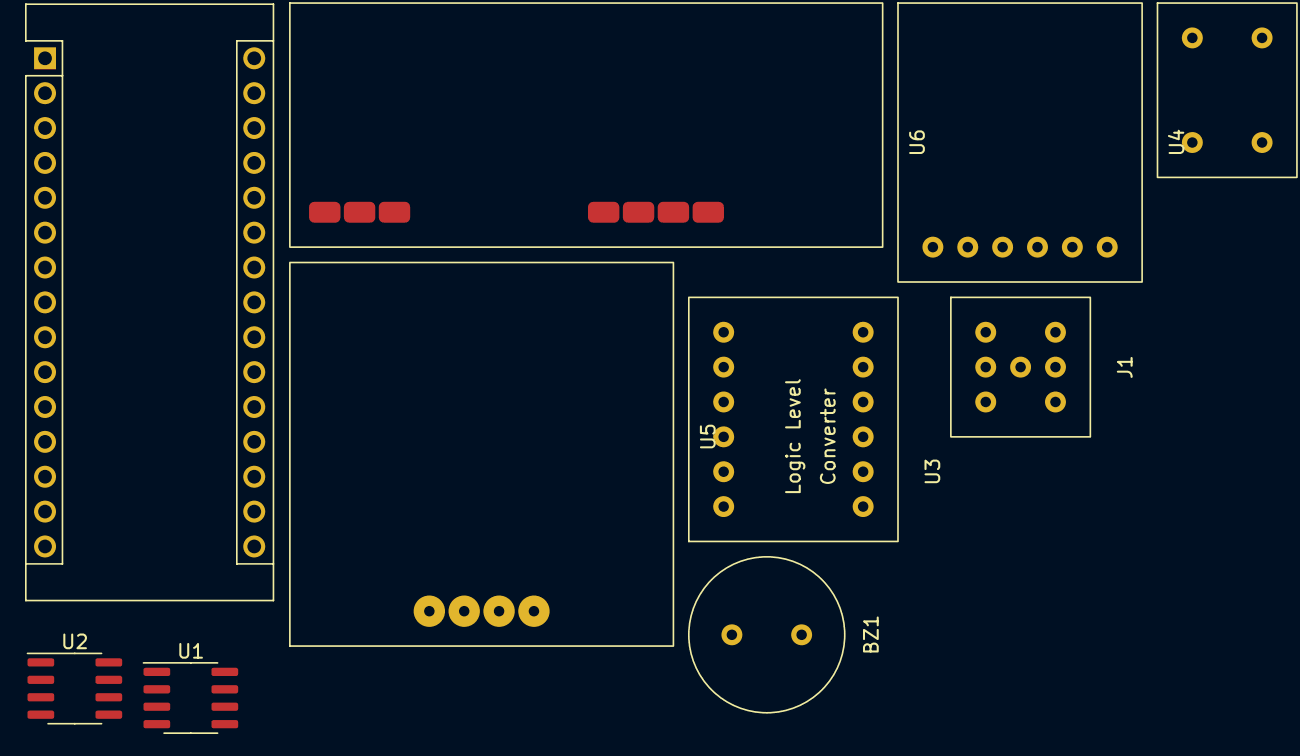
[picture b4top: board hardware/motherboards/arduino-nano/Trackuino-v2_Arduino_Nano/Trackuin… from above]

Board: 2 copper layers, 10 parts (0 on the bottom side), 17 nets, no tracks yet.

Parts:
A1: Arduino_Nano_Every; Arduino_Nano
BZ1: Buzzer
J1: Conn_Coaxial; SMA Jack
SW1: SW_Push_Dual; Button
U1, U2: TMP36xS; SOIC-8_3.9x4.9mm_P1.27mm
U3: Logic Level Converter - Bi-Directional
U4: OpenLog
U5: GPS
U6: Radiometrix HX1

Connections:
+3.3V: U3.9 (LV), U4.4 (VCC)
+5V: A1.27 (+5V), U1.8 (+Vs), U2.8 (+Vs), U3.3 (HV), U5.4 (VIN), U6.5 (VCC)
GND: A1.4 (GND), A1.29 (GND), BZ1.2 (+), SW1.4, U1.4 (GND), U2.4 (GND), U3.4 (GND), U3.10 (GND), U4.5 (GND), U5.3 (GND), U6.6 (GND)
unnamed: A1.3 (~RESET), SW1.1
unnamed: A1.6 (D3), U6.7 (TXD)
unnamed: A1.7 (D4), U6.4 (EN)
unnamed: A1.8 (D5), U5.2 (RX)
unnamed: A1.9 (D6), U5.1 (TX)
unnamed: A1.19 (A0), U2.1 (Vout)
unnamed: A1.20 (A1), U1.1 (Vout)
unnamed: A1.12 (D9), BZ1.1 (-)
unnamed: J1.2 (Ext), U6.1 (RF_GND), U6.3 (RF_GND2)
unnamed: A1.10 (D7), U3.1 (HV1)
unnamed: A1.11 (D8), U3.2 (HV2)
unnamed: U3.7 (LV1), U4.3 (TXO)
unnamed: U3.8 (LV2), U4.2 (RXI)
unnamed: J1.1 (In), U6.2 (RF_OUT)

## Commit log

2022-07-06 begining of v2
2022-07-09 additional commenting and documenting
2022-08-02 working on making webpage for config
2022-08-02 config building UI complete (without config comments)
2022-08-02 website -> docs for own github pages
2022-08-02 Create CNAME
2022-08-02 website redirect and removed debug logs
2022-08-03 setup for arduino builds
2022-08-10 schematics and bom
2022-08-10 added custom libraries
2022-08-11 finished nano board
2023-05-08 start of receiver project
2023-05-11 refactoring stucture + ground station docs
2023-05-11 adding readmes
2023-05-15 docs updates
2023-05-15 removed .next
2023-05-16 ground station status monitoring
2023-05-16 removing station-monitor
2023-05-16 oracle setup in readme
2023-05-16 testing oracle deployment
2023-05-16 404 error handling
2023-05-17 moved tailwind to cli
2023-05-18 netdata tracking and server logging
2023-05-20 license and readme for og trackuino
2023-05-22 netdata monitoring
2023-05-23 server restructuring
2023-05-29 api page only updates when focused
2023-05-30 python-box for config
2023-05-30 ignore config
2023-05-30 removed config
2023-05-30 fully customizable status page
2023-05-30 groundwork for workers and db
2023-06-06 setting up new server architecture
2023-06-07 Refactored to api only
2023-08-09 putting it all together...
2023-08-21 almost working hardware HAB code
2023-08-21 Satellite integration
2023-08-22 first full packaging of code (untested, but compiles)
2024-01-23 Add hardware schematics and designs
    Woohoo! There's hardware!
2024-03-07 webpage code
2024-03-17 dorji library
2024-03-17 fixed readme numbering
2024-03-17 cleaning up kicad dirs
2024-03-17 cleaning up dobor2
2024-03-17 cleaning up files
2024-03-17 remove hardware folder
2024-03-18 adding position and telemetry to db
2024-03-18 working upload functionality
2024-03-18 fixed ip logging
2024-03-18 ip try 2
2024-03-18 removing non-ip chars
2024-03-18 ability to pull bulk data to sync ground stations
2024-03-18 bulk upload w/ timestamp preservation working
2024-03-18 debugging ip get sync on prod
2024-03-18 logging ip addition timeline
2024-03-18 returning since logs are broken
2024-03-18 querying by callsign and timestamp now working
2024-03-18 want to return message timestampes as well
2024-03-18 cant json convert tuples, switched to dict
2024-03-18 formatting json
2024-03-18 fixed sync route
2024-03-20 fixed broadcast loop; ig char is ambiguously default signed
2024-03-29 direwolf changes and rock7 api
2024-03-29 rock7 needs 200
2024-04-10 adding backend mqtt syncing
2024-04-10 python init modules
2024-04-10 moving mqtt syncer
2024-04-10 fixing mqtt syncer
2024-04-10 logging and saving to mqtt sync
2024-04-10 forgot to cast lat long and course to floats
2024-04-10 adding ip to source
2024-04-10 updating mqtt from db
2024-04-10 fixed helpers mqtt sync
2024-04-10 fixed telemtry upload process
2024-04-10 mqtt syncer
2024-04-10 fixing telemetry info
2024-04-10 removed retain timeout for telem
2024-04-10 telemetry values as seperate keys in mqtt
2024-04-10 forgot to specify decimal places...
2024-04-10 debugging tasks
2024-04-10 debugging position save error
2024-04-10 debug position fail
2024-04-10 fixed geo point parsing
2024-04-10 debugging position updating
2024-04-10 removed geo and fixed rock7
2024-04-10 debugging why db to mqtt not working
2024-04-10 misnamed file
2024-04-10 modifying mqtt upload task
2024-04-10 only publish changed telem, and lwt
2024-04-10 changed key format for old data
2024-04-10 same as last just right this time
2024-04-10 rock callsign silly
2024-04-10 shouldnt add to messages if no pos
2024-04-10 debugging
2024-04-11 hopefully fixed redis
2024-04-11 debugging why telem stopped
2024-04-11 forgot an indent
2024-04-11 testing telem upload
2024-04-11 always upload telem as it comes
2024-04-11 debuggingggg
2024-04-11 allow uploading on receive if unique
2024-04-11 debug
2024-04-11 added add debugs
2024-04-11 dicts mutable
2024-04-11 fixed ordering of key assignments
2024-04-11 parse data for rock
2024-04-11 hopefully final rock7 version
2024-04-11 rock7 cs overrides
2024-04-11 adding tail back lookup
2024-04-11 fixed broken telem update task
2024-04-11 silly vscode
2024-04-11 silly key changes
2024-04-11 tail old data endpoint working
2024-04-11 enabled cors for api
2024-04-11 fixed rock7 again
2024-04-11 plz work rock7
2024-04-11 fixed item adding for rock7
2024-04-11 fixed map icons
2024-04-11 adding correct timestamp
2024-04-11 added timestamps
2024-04-11 changing timestamp again
2024-04-11 forgot last updated
2024-04-12 json serialize timestamp broke
2024-04-12 umich balloons frontend
2024-04-12 mqtt sync name for lwt fix
2024-04-12 mqtt again
2024-04-12 uploaded new ino
2024-04-13 messed up speed tail key
2024-04-13 added aprs syncing to backend
2024-04-14 updating aprs item adding
2024-04-14 updating frontend
2024-04-14 aprs obj decode failed
2024-04-14 updated vehicle tracker software
2024-04-14 updated website for apple pwa
2024-04-14 reduced online verbosity
2024-04-14 done for tonight
2024-04-14 why no sync mqtt
2024-04-14 mqtt and aprs need own threads
2024-04-14 backend fixes
2024-04-14 aprs parse
2024-04-14 aprs
2024-04-14 rock7
2024-04-14 broken mph parsing
2024-07-08 modifying service worker for ignoring bad data
2024-07-15 mqtt changes
2024-07-15 mqtt debugging
2024-07-15 mqtt add positions
2024-07-15 maybe found an issue
2024-07-15 debugging web interface telemetry data
2024-07-15 debugging telemetry data
2024-07-15 mqtt print everything
2024-07-15 mqtt parse int
2024-07-15 nan fixing
2024-07-15 parse int debugging
2024-07-15 removing quotes
2024-07-15 updating for solar use
2024-07-16 debugging no data
2024-07-16 which one isnt sending
2025-02-18 migrating to new project location
